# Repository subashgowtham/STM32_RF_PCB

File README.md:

# 4-Layer RF STM32 PCB Design
## Overview
This repository contains the design files for a 4-layer PCB featuring an STM32 microcontroller and RF components. The design is optimized for signal integrity and efficient RF performance, suitable for embedded applications requiring wireless communication.
## Layer Stackup
1. **Top Layer**: Signal traces and critical RF components.
2. **Inner Layer 1**: Ground plane for noise isolation.
3. **Inner Layer 2**: Power plane for stable power distribution.
4. **Bottom Layer**: Signal traces and supplementary components.

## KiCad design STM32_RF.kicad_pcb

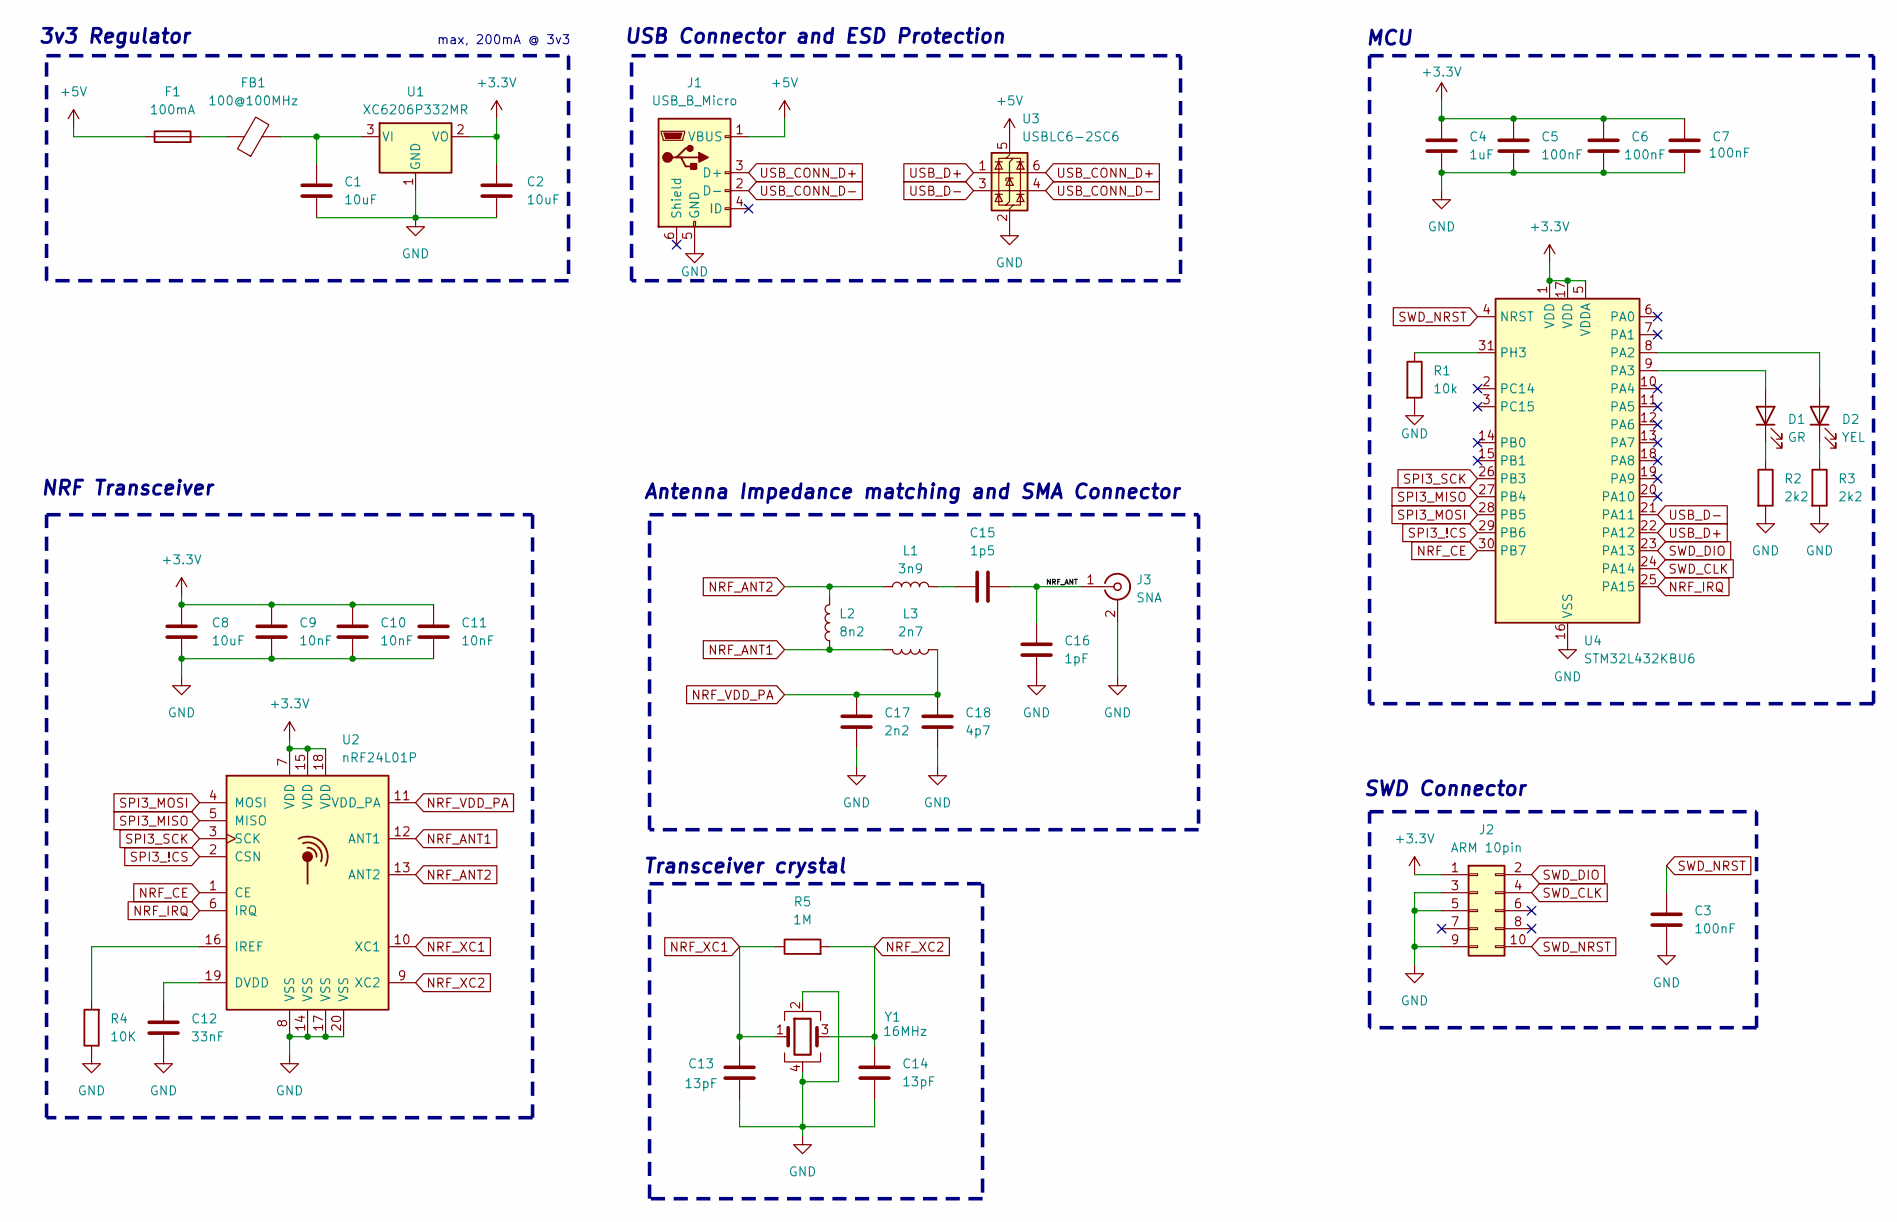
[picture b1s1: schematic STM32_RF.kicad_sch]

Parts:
C1, C2: 10uF; C_0603_1608Metric
C3, C5, C6, C7: 100nF; C_0402_1005Metric
C4: 1uF; C_0402_1005Metric
C8: 10uF; C_0201_0603Metric
C9, C10, C11: 10nF; C_0402_1005Metric
C12: 33nF; C_0402_1005Metric
C13, C14: 13pF; C_0402_1005Metric
C15: 1p5; C_0402_1005Metric
C16: 1pF; C_0402_1005Metric
C17: 2n2; C_0402_1005Metric
C18: 4p7; C_0402_1005Metric
D1: GR; LED_0603_1608Metric
D2: YEL; LED_0603_1608Metric
F1: 100mA; Fuse_1206_3216Metric
FB1: 100@100MHz; L_0805_2012Metric
J1: USB_B_Micro; USB_Micro-B_Molex-105017-0001
J2: ARM 10pin; PinHeader_2x05_P1.27mm_Vertical
J3: SNA; SAMTEC_SMA-J-P-H-ST-EM1
L1: 3n9; L_0402_1005Metric
L2: 8n2; L_0402_1005Metric
L3: 2n7; L_0402_1005Metric
R1: 10k; R_0402_1005Metric
R2, R3: 2k2; R_0603_1608Metric
R4: 10K; R_0402_1005Metric
R5: 1M; R_0402_1005Metric
U1: XC6206P332MR; SOT-23-3
U2: nRF24L01P; QFN-20-1EP_4x4mm_P0.5mm_EP2.5x2.5mm
U3: USBLC6-2SC6; SOT-23-6
U4: STM32L432KBU6; QFN-32-1EP_5x5mm_P0.5mm_EP3.45x3.45mm
Y1: 16MHz; Crystal_SMD_3225-4Pin_3.2x2.5mm

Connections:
+3.3V: C2.1, C4.1, C5.1, C6.1, C7.1, C8.1, C9.1, C10.1, C11.1, J2.1, U1.2 (VO), U2.7 (VDD), U2.15 (VDD), U2.18 (VDD), U4.1 (VDD), U4.5 (VDDA), U4.17 (VDD)
+5V: F1.1, J1.1 (VBUS), U3.5 (VBUS)
/NRF_ANT: C15.2, C16.1, J3.1 (In)
GND: C1.2, C2.2, C3.2, C4.2, C5.2, C6.2, C7.2, C8.2, C9.2, C10.2, C11.2, C12.2, C13.1, C14.2, C16.2, C17.2, C18.2, J1.5 (GND), J2.3, J2.5, J2.9, J3.2 (Ext), R1.2, R2.2, R3.2, R4.1, U1.1 (GND), U2.8 (VSS), U2.14 (VSS), U2.17 (VSS), U2.20 (VSS), U2.21, U3.2 (GND), U4.16 (VSS), U4.32 (VSS), U4.33 (VSS), Y1.2, Y1.4
NRF_ANT1: L2.1, L3.2, U2.12 (ANT1)
NRF_ANT2: L1.1, L2.2, U2.13 (ANT2)
NRF_CE: U2.1 (CE), U4.30 (PB7)
NRF_IRQ: U2.6 (IRQ), U4.25 (PA15)
NRF_VDD_PA: C17.1, C18.1, L3.1, U2.11 (VDD_PA)
NRF_XC1: C13.2, R5.1, U2.10 (XC1), Y1.1
NRF_XC2: C14.1, R5.2, U2.9 (XC2), Y1.3
unnamed: C15.1, L1.2
unnamed: D1.2 (A), U4.9 (PA3)
unnamed: D1.1 (K), R2.1
unnamed: D2.2 (A), U4.8 (PA2)
unnamed: D2.1 (K), R3.1
unnamed: F1.2, FB1.1
unnamed: C1.1, FB1.2, U1.3 (VI)
unnamed: C12.1, U2.19 (DVDD)
unnamed: R4.2, U2.16 (IREF)
unnamed: R1.1, U4.31 (PH3)
SPI3_!CS: U2.2 (CSN), U4.29 (PB6)
SPI3_MISO: U2.5 (MISO), U4.27 (PB4)
SPI3_MOSI: U2.4 (MOSI), U4.28 (PB5)
SPI3_SCK: U2.3 (SCK), U4.26 (PB3)
SWD_CLK: J2.4, U4.24 (PA14)
SWD_DIO: J2.2, U4.23 (PA13)
SWD_NRST: C3.1, J2.10, U4.4 (NRST)
USB_CONN_D+: J1.3 (D+), U3.6 (I/O1)
USB_CONN_D-: J1.2 (D-), U3.4 (I/O2)
USB_D+: U3.1 (I/O1), U4.22 (PA12)
USB_D-: U3.3 (I/O2), U4.21 (PA11)

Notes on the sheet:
MCU
SWD Connector
max, 200mA @ 3v3
USB Connector and ESD Protection
Antenna Impedance matching and SMA Connector
3v3 Regulator
Transceiver crystal
NRF Transceiver

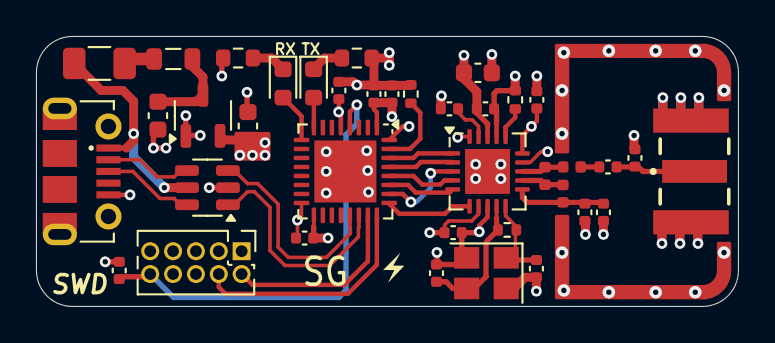
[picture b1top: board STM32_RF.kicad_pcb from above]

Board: 4 copper layers, 39.0 x 15.0 mm, 38 parts (0 on the bottom side), 32 nets.

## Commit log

2024-12-29 first commit
    date: 29-12-2024
